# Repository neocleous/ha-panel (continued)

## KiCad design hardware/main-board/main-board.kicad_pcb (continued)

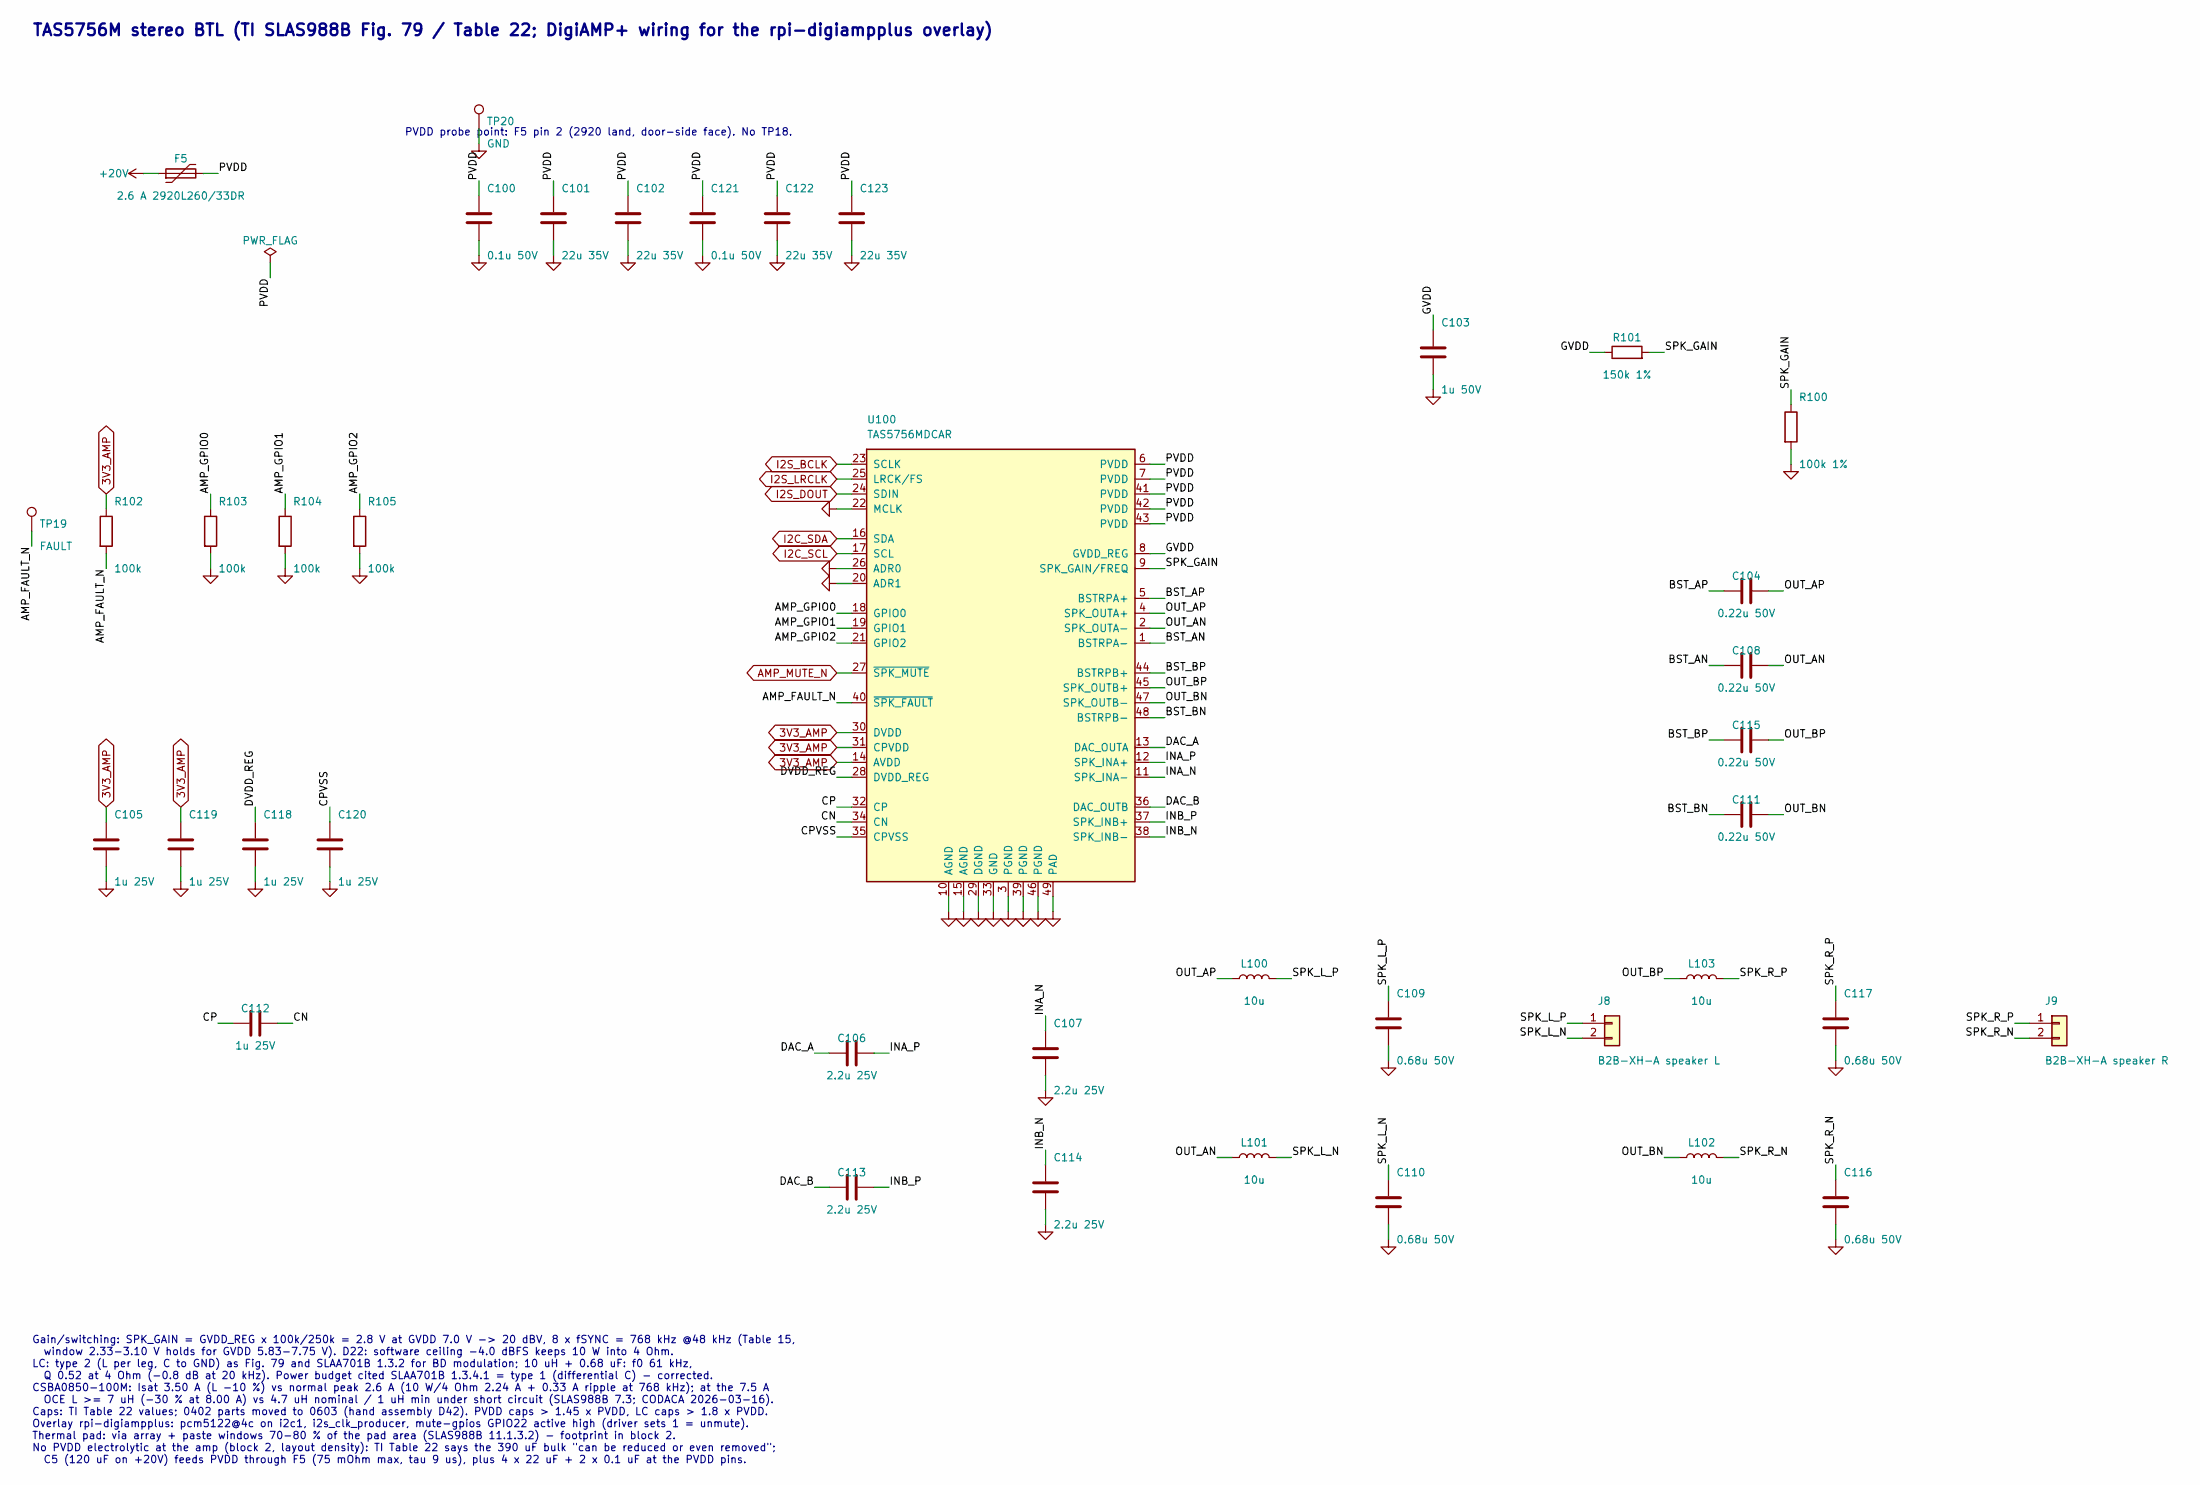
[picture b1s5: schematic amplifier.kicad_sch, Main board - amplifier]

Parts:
C100, C121: 0.1u 50V; C_0603_1608Metric; MPN CC0603KRX7R9BB104; DigiKey 311-1344-1-ND
C101, C102, C122, C123: 22u 35V; C_0805_2012Metric; MPN GMC21X5R226M35NT; DigiKey 4713-GMC21X5R226M35NTCT-ND
C103: 1u 50V; C_0603_1608Metric; MPN UMK107AB7105KA-T; DigiKey 587-3247-1-ND
C104, C108, C111, C115: 0.22u 50V; C_0603_1608Metric; MPN CL10B224KB8NNNC; DigiKey 1276-CL10B224KB8NNNCCT-ND
C105, C112, C118, C119, C120: 1u 25V; C_0603_1608Metric; MPN CC0603KRX7R8BB105; DigiKey 311-1802-1-ND
C106, C107, C113, C114: 2.2u 25V; C_0603_1608Metric; MPN CC0603KRX7R7BB225; DigiKey 311-3490-1-ND
C109, C110, C116, C117: 0.68u 50V; C_0805_2012Metric; MPN CL21B684KBFVPNE; DigiKey 1276-7009-1-ND
F5: 2.6 A 2920L260/33DR; Fuse_2920_7451Metric; MPN 2920L260/33DR; DigiKey 18-2920L260/33DRCT-ND
J8: B2B-XH-A speaker L; JST_XH_B2B-XH-A_1x02_P2.50mm_Vertical; MPN B2B-XH-A; DigiKey 455-B2B-XH-A-ND
J9: B2B-XH-A speaker R; JST_XH_B2B-XH-A_1x02_P2.50mm_Vertical; MPN B2B-XH-A; DigiKey 455-B2B-XH-A-ND
L100, L101, L102, L103: 10u; L_Codaca_CSBA0850; MPN CSBA0850-100M; DigiKey 4044-CSBA0850-100MCT-ND
R100: 100k 1%; R_0603_1608Metric; MPN RMCF0603FT100K; DigiKey RMCF0603FT100KCT-ND
R101: 150k 1%; R_0603_1608Metric; MPN RC0603FR-07150KL; DigiKey 311-150KHRCT-ND
R102, R103, R104, R105: 100k; R_0603_1608Metric; MPN RMCF0603FT100K; DigiKey RMCF0603FT100KCT-ND
TP19: FAULT; TestPoint_Pad_D1.5mm
TP20: GND; TestPoint_Pad_D1.5mm
U100: TAS5756MDCAR; TI_DCA0048A_HTSSOP-48-1EP; MPN TAS5756MDCAR; DigiKey 296-40565-1-ND

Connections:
3V3_AMP: C105.1, C119.1, R102.1, U100.14 (AVDD), U100.30 (DVDD), U100.31 (CPVDD); also elsewhere on the board
+20V: F5.1; also elsewhere on the board
/Amplifier/AMP_FAULT_N: R102.2, TP19.1, U100.40 (~SPK_FAULT)
/Amplifier/AMP_GPIO0: R103.1, U100.18 (GPIO0)
/Amplifier/AMP_GPIO1: R104.1, U100.19 (GPIO1)
/Amplifier/AMP_GPIO2: R105.1, U100.21 (GPIO2)
/Amplifier/BST_AN: C108.1, U100.1 (BSTRPA-)
/Amplifier/BST_AP: C104.1, U100.5 (BSTRPA+)
/Amplifier/BST_BN: C111.1, U100.48 (BSTRPB-)
/Amplifier/BST_BP: C115.1, U100.44 (BSTRPB+)
/Amplifier/CN: C112.2, U100.34 (CN)
/Amplifier/CP: C112.1, U100.32 (CP)
/Amplifier/CPVSS: C120.1, U100.35 (CPVSS)
/Amplifier/DAC_A: C106.1, U100.13 (DAC_OUTA)
/Amplifier/DAC_B: C113.1, U100.36 (DAC_OUTB)
/Amplifier/DVDD_REG: C118.1, U100.28 (DVDD_REG)
/Amplifier/GVDD: C103.1, R101.1, U100.8 (GVDD_REG)
/Amplifier/INA_N: C107.1, U100.11 (SPK_INA-)
/Amplifier/INA_P: C106.2, U100.12 (SPK_INA+)
/Amplifier/INB_N: C114.1, U100.38 (SPK_INB-)
/Amplifier/INB_P: C113.2, U100.37 (SPK_INB+)
/Amplifier/OUT_AN: C108.2, L101.1, U100.2 (SPK_OUTA-)
/Amplifier/OUT_AP: C104.2, L100.1, U100.4 (SPK_OUTA+)
/Amplifier/OUT_BN: C111.2, L102.1, U100.47 (SPK_OUTB-)
/Amplifier/OUT_BP: C115.2, L103.1, U100.45 (SPK_OUTB+)
/Amplifier/PVDD: C100.1, C101.1, C102.1, C121.1, C122.1, C123.1, F5.2, U100.6 (PVDD), U100.7 (PVDD), U100.41 (PVDD), U100.42 (PVDD), U100.43 (PVDD)
/Amplifier/SPK_GAIN: R100.1, R101.2, U100.9 (SPK_GAIN/FREQ)
/Amplifier/SPK_L_N: C110.1, J8.2, L101.2
/Amplifier/SPK_L_P: C109.1, J8.1, L100.2
/Amplifier/SPK_R_N: C116.1, J9.2, L102.2
/Amplifier/SPK_R_P: C117.1, J9.1, L103.2
AMP_MUTE_N: U100.27 (~SPK_MUTE); also elsewhere on the board
GND: C100.2, C101.2, C102.2, C103.2, C105.2, C107.2, C109.2, C110.2, C114.2, C116.2, C117.2, C118.2, C119.2, C120.2, C121.2, C122.2, C123.2, R100.2, R103.2, R104.2, R105.2, TP20.1, U100.3 (PGND), U100.10 (AGND), U100.15 (AGND), U100.20 (ADR1), U100.22 (MCLK), U100.26 (ADR0), U100.29 (DGND), U100.33 (GND), U100.39 (PGND), U100.46 (PGND), U100.49 (PAD); also elsewhere on the board
I2C_SCL: U100.17 (SCL); also elsewhere on the board
I2C_SDA: U100.16 (SDA); also elsewhere on the board
I2S_BCLK: U100.23 (SCLK); also elsewhere on the board
I2S_DOUT: U100.24 (SDIN); also elsewhere on the board
I2S_LRCLK: U100.25 (LRCK/FS); also elsewhere on the board

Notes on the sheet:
TAS5756M stereo BTL (TI SLAS988B Fig. 79 / Table 22; DigiAMP+ wiring for the rpi-digiampplus overlay)
PVDD probe point: F5 pin 2 (2920 land, door-side face). No TP18.
Gain/switching: SPK_GAIN = GVDD_REG x 100k/250k = 2.8 V at GVDD 7.0 V -> 20 dBV, 8 x fSYNC = 768 kHz @48 kHz (Table 15, window 2.33-3.10 V holds for GVDD 5.83-7.75 V). D22: software ceiling -4.0 dBFS keeps 10 W into 4 Ohm. LC: type 2 (L per leg, C to GND) as Fig. 79 and SLAA701B 1.3.2 for BD modula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

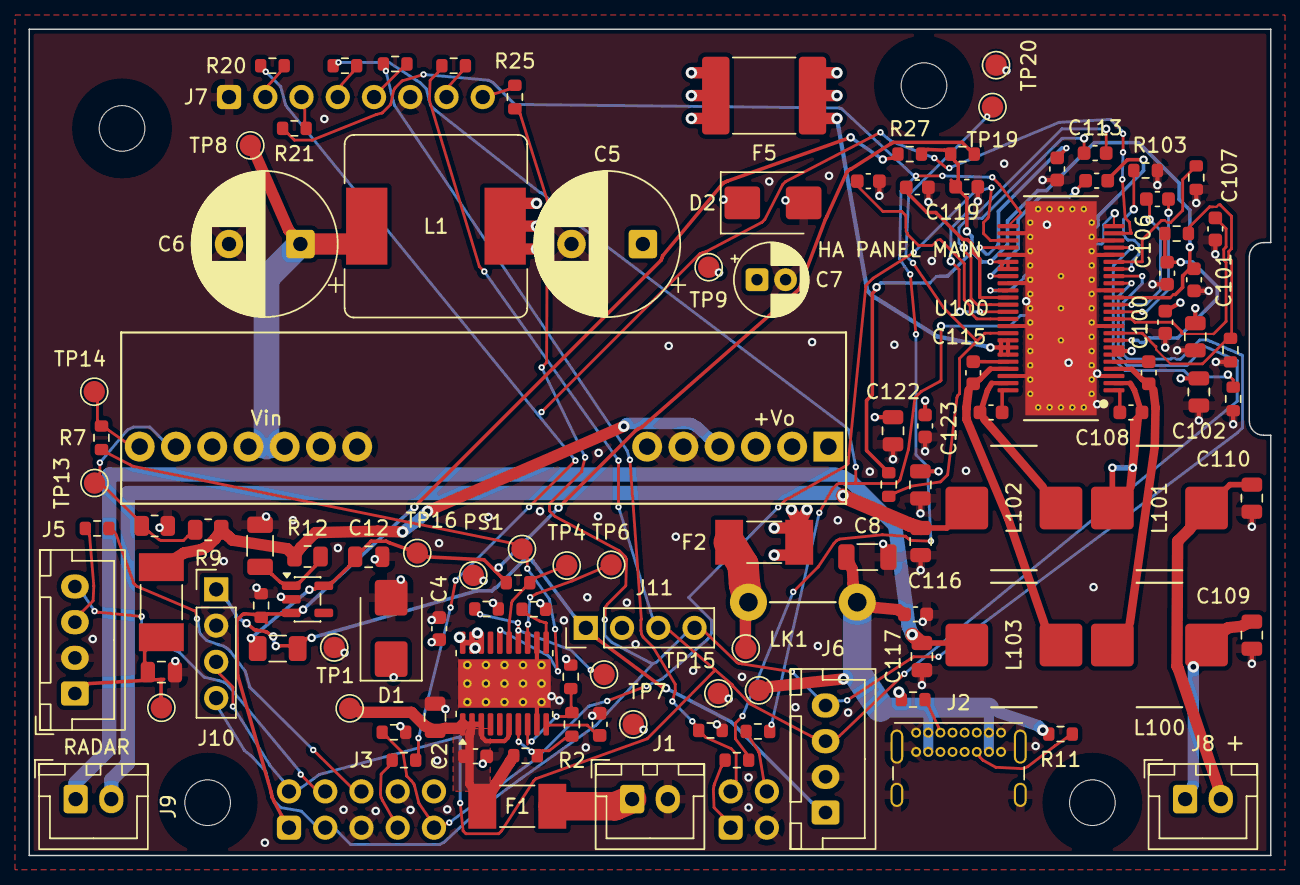
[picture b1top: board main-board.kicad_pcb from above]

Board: 4 copper layers, 87.0 x 57.9 mm, 120 parts (0 on the bottom side), 74 nets.

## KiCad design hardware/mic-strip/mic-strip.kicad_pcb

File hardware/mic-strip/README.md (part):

# HA panel — mic strip (two boards of one design)

Status: **block 3 done (2026-11-09) — fab files, assembly notes and drawing issued.** Decision 9 → **option 1** (Daniel, 2026-11-08): soldered wire pads instead of the JST connector. Decision 10 → **option 1** (Daniel, 2026-11-08): ESD321DYAR for D1–D3. JLC upload: **`fab/mic-strip-jlc-2026-11-09.zip`** (vias 0.5/0.3, D63 = b); order options in `../notes/jlc-fab.md` (0.8 mm, 2 layers, ENIG — Daniel, 2026-11-08). Assembly drawing: `mic-strip-assembly.pdf`; assembly and bring-up: below.

- **KiCad 9.0.9.** Open `mic-strip.kicad_pro`. Project libraries: `lib/ha_panel.kicad_sym` (IM69D120) and `lib/ha_panel.pretty` (IM69D120 land pattern, 5-pad wire column, heat-stake hole).
- **Schematic PDF:** `mic-strip-schematic.pdf`. **ERC:** 0 errors, 0 warnings (`erc-report.txt`).
- **DRC (2026-11-09, all severities):** 0 violations, 0 unconnected, 0 footprint errors, schematic parity clean (`drc-report.txt`). The check "footprint differs from library" is set to *ignore* in `mic-strip.kicad_pro`. U1's and MK1's silk marks at the board edge were removed on purpose, so both footprints differ from their library copies. These were the 2 warnings until 2026-11-08.
- **Renders:** `mic-strip-3d.png` (front = gasket side, back = parts) and `mic-strip-copper-F-B.png` (front copper, back copper mirrored). The copper picture shows the 2026-11-09 routing; the 3D render is from 2026-11-07, with the same parts and silk.
- **Generated by** `../main-board/gen/mic_strip.py` (schematic), `../main-board/gen/pcb_mic.py` (layout), `fix_esd321.py` (decision 10.1) and `reroute_strip_vias.py` (D63 = b). The KiCad files are the source of truth.

## Board (rev F K21 / "Top cap")
- **28 × 6 × 0.8 mm, 2 layers.** x = 0 at the outer (port) end. Every part sits on the **back** (inner side); the front faces the 1.0 mm gasket and carries only the GND pour and short crossings.
- **Port:** NPTH Ø0.8 at (2.0, 3.0), under MK1's sound port (rev F port at x_rel ±35.5, strip outer end ±37.5).
- **Heat-stake holes:** NPTH Ø2.0 at (7.5, 3.0) and (26.0, 3.0) for the Ø1.8 pins (x_rel ±30.0 / ±11.5); Ø3.6 back keep-outs (no copper, no parts) for the staked heads.
- One design for both sides: the left strip is the right one turned 180° in the cap plane (port end outward, gasket side up).
- **Rules:**
  - tracks 0.2 (0.25–0.3 for supply and ground), clearance 0.15, copper to edge 0.3;
  - **vias 0.5/0.3**, ring 0.10;
  - minimum via diameter 0.5 and minimum hole 0.3 (raised from 0.45 / 0.2 on 2026-11-09, so DRC flags any via outside JLC's free class);
  - hole clearance 0.25, hole to hole 0.25.
  - JLC capabilities checked 2026-11-07 and 2026-11-09 (`../notes/jlc-fab.md`).
- **Vias, D63 = (b) (Daniel, 2026-11-09):** **28 × 0.45/0.2 → 25 × 0.5/0.3.** JLC's order page states its 0.2 mm exemption only for multilayer boards; 0.3 mm holes are the free class.
  - Placement, parts, pads and silk are unchanged. Every track and via was re-routed by `reroute_strip_vias.py`, with the same connections and widths as `pcb_mic.py`.
  - Three fewer vias:
    - R2 (100 kΩ pull-down, no current) reaches GND through U1's ground on the back and has no via of its own. Its via was one of the two GND vias that a plain re-drill would have left 0.24 mm apart.
    - The back GND route from R2 to C1, which took two vias, is dropped. C1 has its own via and both pours carry ground.
  - One /MIC_LR vertex on the front was moved 0.05 mm inward to keep 0.3 from the edge.
  - **Achieved:**
    - ring 0.10;
    - via hole to hole ≥ 0.45 (different nets; JLC 0.2);
    - via hole to NPTH ≥ 0.56;
    - via hole to other-net track ≥ 0.29 and to other-net pad ≥ 0.33 (board 0.25; JLC 0.2).

## Circuit (E0-D6, decisions 8.1 and 9.1)
| Ref | Part | Default | Why / source |
|---|---|---|---|
| J1 | 5 SMD wire pads 2.0 × 0.7, 1.1 mm pitch, one column across the strip | — | Decision 9.1: the BM05B-SRSS-TB (8.89 mm courtyard) does not fit beside the parts. Cable JST A05SR05SR30K305B with both housings cut off, conductors soldered in cable order **1 VDD, 2 GND, 3 CLK, 4 SEL, 5 DATA**; hot-melt strain relief over the pads. The pads are also the test points. |
| D1–D3 | TI ESD321DYAR, SOD-523 | fitted | ESD on VDD, CLK, DATA next to the cable pads. Decision 10.1: replaces TPD1E05U06DYAR (DigiKey 0 stock, 26 weeks, 2026-11-08). 0.9 pF typ / 1.1 pF max, VRWM 3.6 V above the 3.3 V lines. **DYA pinout: pin 1 = GND, pin 2 = IO** — the reverse of the TPD1E05U06, so the footprints are turned 180° (copper unchanged). Pin 1 is the end marked by the dot on the body (TI marks the DYA pin 1 with a circular notch, not a line); it goes to the closed end of the silk bracket, the GND pad at x 19.8. Check after soldering, meter in diode mode: red on the GND pad, black on the signal pad → conducts; reversed → open. Generated by `../main-board/gen/fix_esd321.py`. |
| R1 | 100 Ω 0603 | fitted | VDD RC filter with C1: f_c = 159 Hz; drop ≈ 0.1 V at the mic's 980 µA. |
| C1, C2 | 10 µF 10 V X5R 0603, 100 nF 50 V X7R 0603 | fitted | Mic decoupling (E0-D6); C2 next to MK1's VDD pin. |
| U1 | TI SN74LVC1G17DCKR, SC-70-5 | fitted | Schmitt buffer re-drives CLK next to the mic (E0-D6). C3 100 nF at VCC. Bypass lever (bench 2.5): remove U1 and bridge its pads 2–4 with wire — R3 (the 0 Ω bypass position) was dropped for space. |
| R2 | 100 kΩ 0603 | fitted | Weak pull-down on the buffer input (CLK may be tri-stated when muted — inference). |
| MK1 | Infineon IM69D120V01XTSA1 | fitted | Decision 8.1. Bottom port, −26 dBFS ±1, SNR 69 dB(A), 3.072 MHz inside its 2.9–3.3 MHz range, clock duty 48–52 %, 980 µA typ, VDD 1.62–3.6 V (datasheet rev 1.0, 2017-12-20). DigiKey IM69D120V01XTSA1CT-ND. |
| R4 | 33 Ω 0603 | fitted | DATA source termination (100 Ω alternative, bench 2.5 lever). |
| R5 | 0 Ω 0603 | fitted | **L/R from the cable SEL wire**, strapped at the ReSpeaker end (vacated mic pad 5): GND = left, VDD = right. Must be fitted on both strips — there is no on-board strap any more (JP1 dropped, decision 9.1). |

Removed against checkpoint 1: J1 connector, JP1, TP1–TP4 (decision 9.1), R3 (space); MSM261DHP006 replaced by the IM69D120 (decision 8.1); TPD1E05U06DYAR replaced by the ESD321DYAR (decision 10.1).

Cable termination at the ReSpeaker (bench plan "connect by function"): VDD → pad 1, CLK → pad 2, DATA → pad 3, GND → pad 4 (and 6), **SEL → pad 5**. SEL is static and sits between CLK and DATA in the cable.

Sources (read 2026-11-07, assembly notes 2026-11-09): Infineon IM69D120 datasheet rev 1.0 (2017-12-20); TI SN74LVC1G17 SCES351Y (https://www.ti.com/lit/ds/symlink/sn74lvc1g17.pdf); TI TPD1E05U06 SLVSBO7O (https://www.ti.com/lit/ds/symlink/tpd1e05u06.pdf); read 2026-11-08: TI ESD321 datasheet rev C, 2025-06-04 (https://www.ti.com/lit/ds/symlink/esd321.pdf, table 4-2) and TI E2E on the DYA pin-1 mark (https://e2e.ti.com/support/interface-group/interface/f/interface-forum/1410599/esd321-pin1-position, https://e2e.ti.com/support/interface-group/interface/f/interface-forum/1449663/esd321-pin-1-clarify); rev F geometry from `claude/enclosure-v5-revF-2026-11-03.md` (Top: mic strips) and `claude/enclosure-v5-revF-audit-response-2026-11-06.md` (finding 38); cable from `claude/E0-order-list-2026-11-01.md` rev 4; JLC capabilities https://jlcpcb.com/capabilities.

## Assembly (block 3, 2026-11-09) — build two identical strips
Drawing: `mic-strip-assembly.pdf` (back, as seen from the back). One hotplate pass, parts side up.

**Before you start**
- Paste: the same Sn63/Pb37 no-clean as the main board, dispensed by syringe. The combined stencil has no strip area (`../notes/jlc-fab.md`).
- Bare strip:
  - hold it against the light: the Ø0.8 port hole must be open;
  - meter: VDD–GND (J1 pads 1–2) open.
- **What the makers say about the port:**
  - Infineon's IM69D120 datasheet (rev 1.0) gives only the reflow qualification: 3 reflows, peak 260 °C, IPC/JEDEC J-STD-020D-01. It has no handling, flux or washing rules.
  - Other makers' bottom-port MEMS guides agree:
    - TDK/InvenSense: water must not reach the port when washing; no blow-off, no ultrasonic cleaning.
    - InvenSense AN-100: the port is sensitive to solder flux.
    - ST: seal the port with tape during soldering.
  - So: no-clean paste, **no washing, no IPA or air near the port**, and Kapton tape over the hole on the front while soldering.

**Build order**
1. Kapton over the port hole on the front (gasket side).
2. Small paste dots on the back pads. Nothing in or next to the port hole.
3. Place:
   - D1–D3 ESD321: pin 1 = GND (dot or notch on the body), at the closed end of the silk bracket;
   - C1 10 µF, C2 100 nF, C3 100 nF;
   - R1 100 Ω, R2 100 kΩ, R4 33 Ω, R5 0 Ω (**required**);
   - U1 SN74LVC1G17 (pin 1 at the chamfer);
   - MK1 last, lid up, port over the hole. Handle it by the lid only.
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
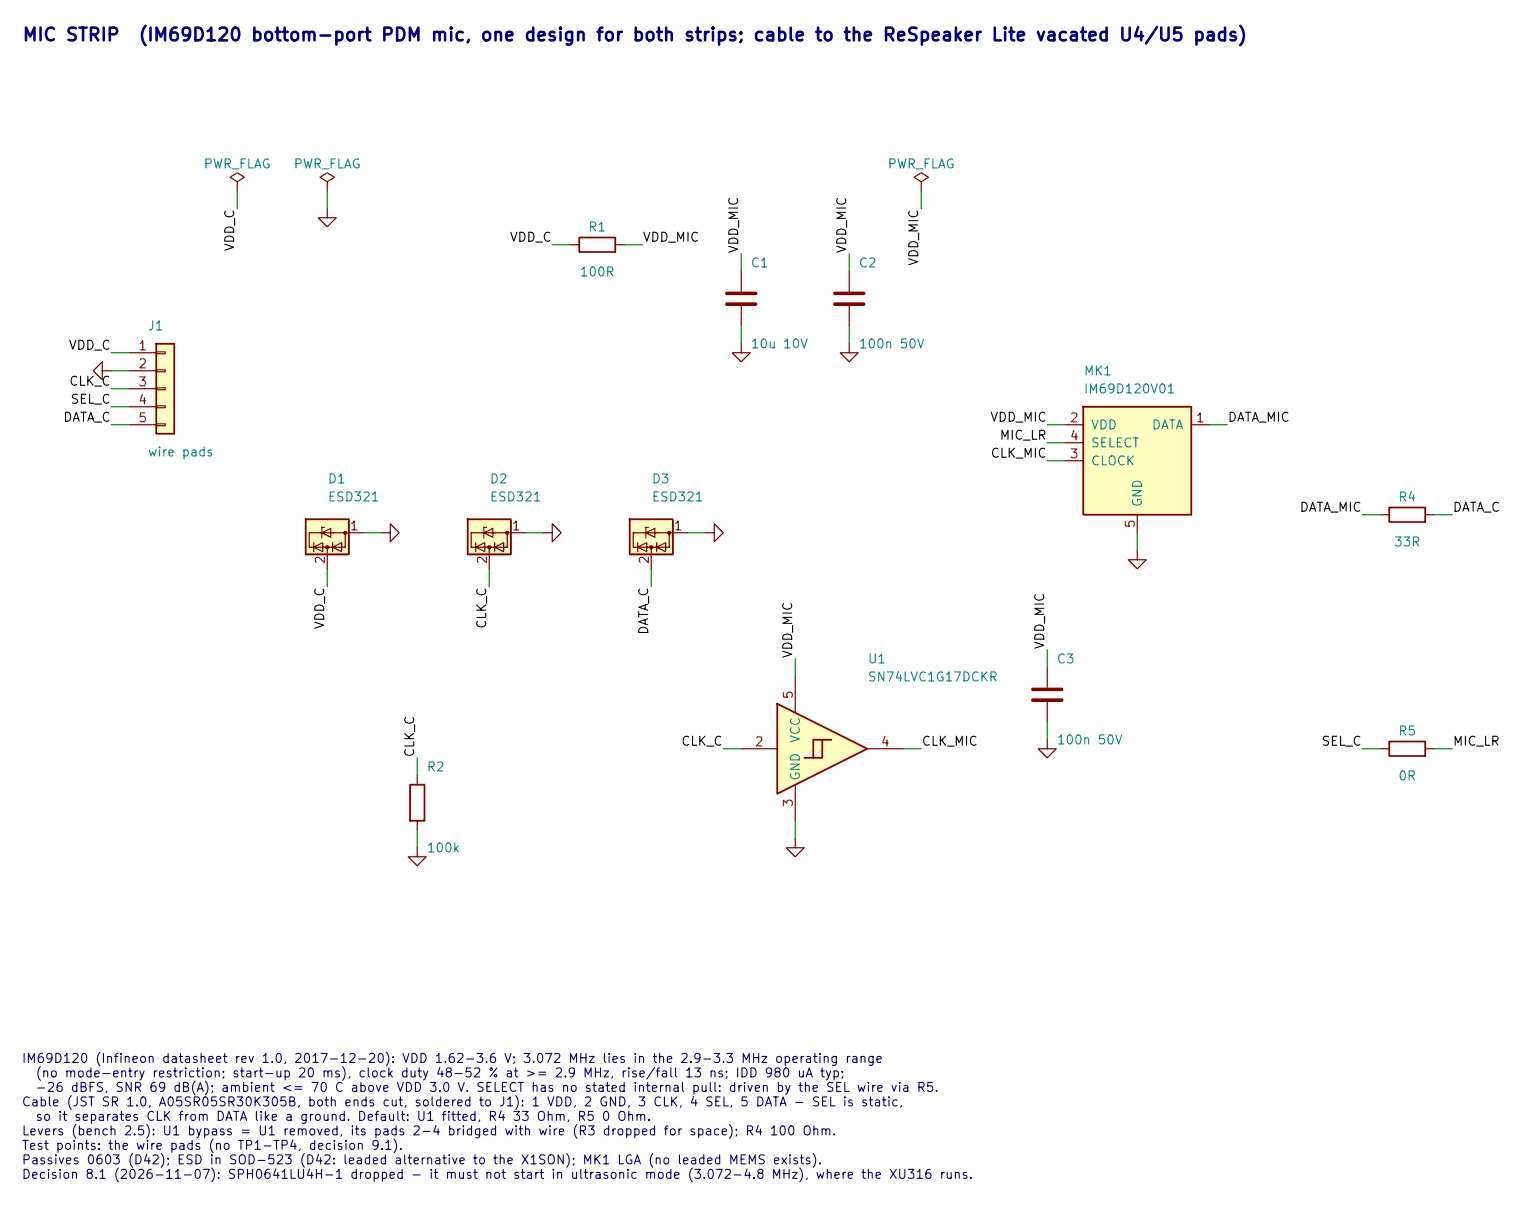
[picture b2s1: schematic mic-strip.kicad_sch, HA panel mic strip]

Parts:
C1: 10u 10V; C_0603_1608Metric; MPN EMK107BBJ106MA-T; DigiKey 587-3238-1-ND
C2, C3: 100n 50V; C_0603_1608Metric; MPN CC0603KRX7R9BB104; DigiKey 311-1344-1-ND
D1, D2, D3: ESD321; D_SOD-523; MPN ESD321DYAR; DigiKey 296-ESD321DYARCT-ND
J1: wire pads; WirePads_1x05_P1.10mm_2.0x0.7mm
MK1: IM69D120V01; Infineon_IM69D120_PG-LLGA-5-1; MPN IM69D120V01XTSA1; DigiKey IM69D120V01XTSA1CT-ND
R1: 100R; R_0603_1608Metric; MPN RMCF0603FT100R; DigiKey RMCF0603FT100RCT-ND
R2: 100k; R_0603_1608Metric; MPN RMCF0603FT100K; DigiKey RMCF0603FT100KCT-ND
R4: 33R; R_0603_1608Metric; MPN RMCF0603FT33R0; DigiKey RMCF0603FT33R0CT-ND
R5: 0R; R_0603_1608Metric; MPN RC0603JR-070RL; DigiKey 311-0.0GRCT-ND
U1: SN74LVC1G17DCKR; SOT-353_SC-70-5; MPN SN74LVC1G17DCKR; DigiKey 296-11934-1-ND

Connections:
/CLK_C: D2.2 (I/O), J1.3, R2.1, U1.2
/CLK_MIC: MK1.3 (CLOCK), U1.4
/DATA_C: D3.2 (I/O), J1.5, R4.2
/DATA_MIC: MK1.1 (DATA), R4.1
/MIC_LR: MK1.4 (SELECT), R5.2
/SEL_C: J1.4, R5.1
/VDD_C: D1.2 (I/O), J1.1, R1.1
/VDD_MIC: C1.1, C2.1, C3.1, MK1.2 (VDD), R1.2, U1.5 (VCC)
GND: C1.2, C2.2, C3.2, D1.1 (GND), D2.1 (GND), D3.1 (GND), J1.2, MK1.5 (GND), R2.2, U1.3 (GND)

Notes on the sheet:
MIC STRIP (IM69D120 bottom-port PDM mic, one design for both strips; cable to the ReSpeaker Lite vacated U4/U5 pads)
IM69D120 (Infineon datasheet rev 1.0, 2017-12-20): VDD 1.62-3.6 V; 3.072 MHz lies in the 2.9-3.3 MHz operating range (no mode-entry restriction; start-up 20 ms), clock duty 48-52 % at >= 2.9 MHz, rise/fall 13 ns; IDD 980 uA typ; -26 dBFS, SNR 69 dB(A); ambient <= 70 C above VDD 3.0 V. SELECT has no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

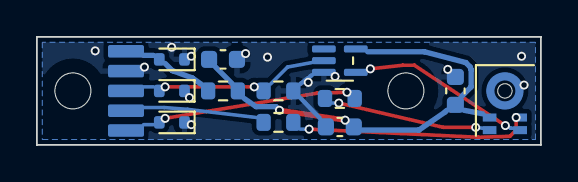
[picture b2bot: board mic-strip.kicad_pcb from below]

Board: 2 copper layers, 28.0 x 6.0 mm, 15 parts (13 on the bottom side), 9 nets.

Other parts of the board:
HS1, HS2: heat stake; HeatStake_D2.0mm_Head3.6mm

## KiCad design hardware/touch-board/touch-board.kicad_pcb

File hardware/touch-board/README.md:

# HA panel — touch board rev D (decision 5A, 2026-11-07)

Replaces rev C (`hardware/rev-c`, unchanged) in the rev F chin seat: same 90 × 44 × 1.6 outline, R2 corners, no holes
except tented vias, flat front. Generated by `hardware/main-board/gen/touch_board.py` (schematic) and `pcb_touch.py`
(layout). KiCad 9.0.9. ERC 0 errors / 0 warnings; DRC (all severities, with schematic parity) 0 violations, 0 unconnected,
0 footprint errors (2026-11-09; `fix_touch_fpid.py` gave every footprint its library nickname, which cleared 12 parity
warnings the error-only DRC had not shown).

| Item | Value | Source |
|---|---|---|
| Controller | AT42QT1070 SOIC-14, comms (I²C) mode, address 0x1B; MODE (pin 2) to GND; RESET, CHANGE, KEY4–6 open | Atmel 9596C–AT42–05/2013 table 1-1 |
| Electrodes | 4 × 16 × 16 mm, r 2, front copper under the mask; centres front-view X 9/33/57/81, Y 13 (rev F) | QTAN0062 §2.3: electrode ≥ 4 × panel thickness; panel ≈ 2.5 wall + 0.7 cloth = 3.2 mm (rev F model, not measured) → ≥ 12.8 mm. Rev C: Ø12 |
| Key order | seen from the front, left to right **KEY0, KEY1, KEY2, KEY3** — the same order as rev C rotated into rev F, so the rev F mapping in `at42qt1070.py` applies unchanged | |
| Series R | R1–R4 4.7 kΩ 0603, next to U1 | datasheet §3.1 |
| Decoupling | C1 100 nF + C2 10 µF 0603 | |
| HOST pads | J1, SMD wire pads 2 × 3 mm at 3.5 pitch on the back, front-view (33, 39.8) as rev F: VCC, GND, SDA, SCL (labelled); lead from main board J6 | rev F lead TOUCH unchanged |
| Sensors | none — the BME680 and VEML6030 leads land on main-board J10 (decision 5A); VL53L0X cluster dropped | |
| Pull-ups | none on this board (Pi 1.8 kΩ) | |
| Cx | AT42QT1070 accepts 1–30 pF per key | datasheet 6.2 |

Layout: front copper = electrodes only. Back: U1, R1–R4, C1, C2, J1 pads, all traces (0.25 mm signal, 0.4 mm supply),
B.Cu track keep-outs behind the electrodes, electrode vias at each electrode's top edge (tented).

**Assembly (2026-11-09).** One SMD side, the back. Drawing: `touch-board-assembly.pdf` (back, as seen from the back).
1. Bare board: VCC–GND on the HOST pads must read open.
2. Paste the back through the touch area of the combined stencil (`../stencil/`).
   - Use the stencil the same way up as for the main board: the touch pattern is already mirrored to match the back seen from above.
   - The HOST pads get no paste.
3. Place U1 (pin 1 at the chamfered corner), C1 100 nF, C2 10 µF, R1–R4 4.7 kΩ.
4. Hotplate with the front face down on a clean sheet (the front has no parts). Same paste and profile as the main board (`../main-board/README.md`).
5. Solder the touch lead to the HOST pads with the iron: VCC, GND, SDA, SCL as labelled. Lead: XH 4P from main-board J6, cut ≈ 105 (`../notes/harness.md`).
6. Bring-up: VCC–GND not shorted; then, on the Pi, `sudo i2cdetect -y 1` shows **1b**.

Files: `touch-board.kicad_sch/.kicad_pcb/.kicad_pro`, `lib/` (ha_panel symbol + footprints), `touch-board-schematic.pdf`,
`erc-report.txt`, `drc-report.txt`, `touch-board-front.png`, `touch-board-back.png`.

**Fab (JLC, bare board; D57):** `fab/touch-board-jlc-2026-11-09.zip` (gerbers and drill, unzipped in `fab/gerbers/`;
`fab/drill-report.txt`: 4 plated holes Ø0.30, the tented electrode vias; no NPTH). 2 layers, 1.6 mm, ENIG, 90 × 44.
Order options and limits: `../notes/jlc-fab.md`. **Paste:** the touch board's back pattern is on the combined stencil
with the main board's front (`../stencil/`); don't tick the stencil box on the touch-board line.

**Purchase fields** (in the schematic; `gen/bom_fields_touch.json`):

| Ref | Part | Source |
|---|---|---|
| U1 | Microchip AT42QT1070-SSUR | Daniel's own stock (D56): none in the DigiKey basket |
| C1 | Yageo CC0603KRX7R9BB104, 100 nF 50 V X7R | DigiKey 311-1344-1-ND, basket line shared with the main board and the strip |
| C2 | Taiyo Yuden EMK107BBJ106MA-T, 10 µF 16 V X5R | DigiKey 587-3238-1-ND, basket line shared with the strip |
| R1–R4 | Yageo RC0603FR-074K7L, 4.7 kΩ 1 % | DigiKey 311-4.70KHRCT-ND, basket line shared with the main board |
| J1 | bare wire pads | — |
| E0–E3 | copper electrodes | — |

The basket lines' quantities already cover these parts within the spares rule (`../notes/digikey-bom.md`).

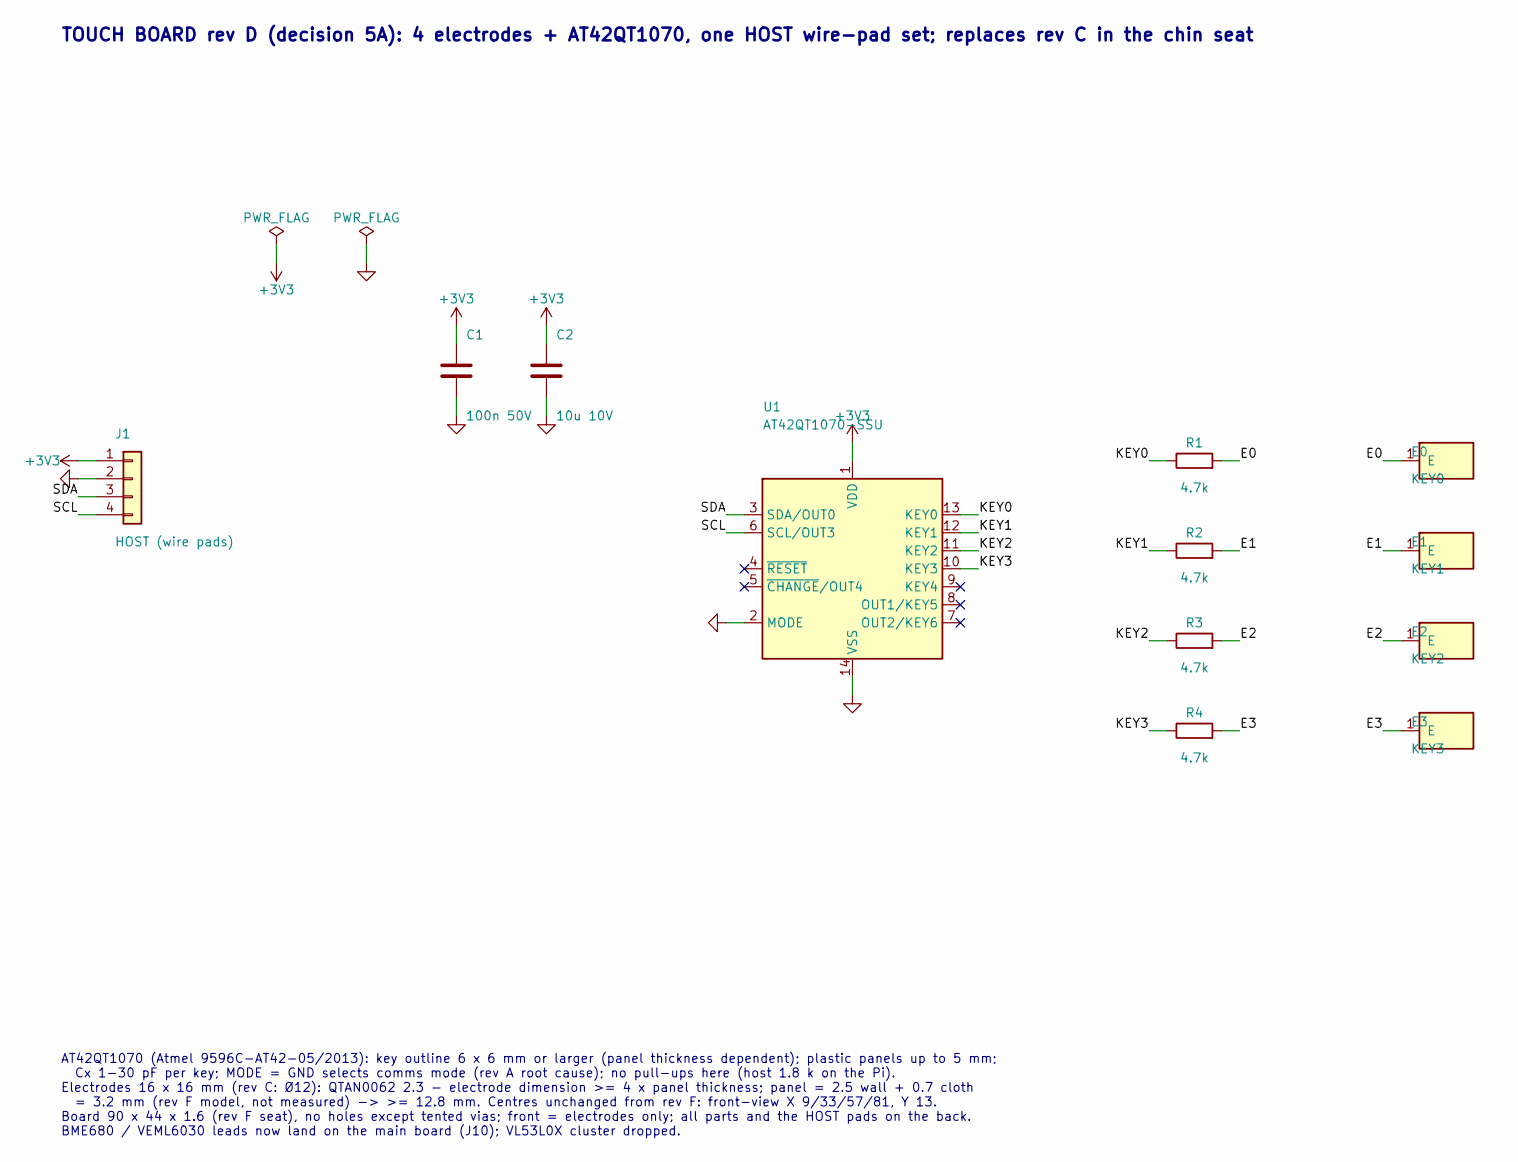
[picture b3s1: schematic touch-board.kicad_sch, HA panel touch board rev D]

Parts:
C1: 100n 50V; C_0603_1608Metric; MPN CC0603KRX7R9BB104; DigiKey 311-1344-1-ND
C2: 10u 10V; C_0603_1608Metric; MPN EMK107BBJ106MA-T; DigiKey 587-3238-1-ND
E0: KEY0; TouchElectrode_16x16mm_R2
E1: KEY1; TouchElectrode_16x16mm_R2
E2: KEY2; TouchElectrode_16x16mm_R2
E3: KEY3; TouchElectrode_16x16mm_R2
J1: HOST (wire pads); WirePads_1x04_P3.50mm_2.0x3.0mm
R1, R2, R3, R4: 4.7k; R_0603_1608Metric; MPN RC0603FR-074K7L; DigiKey 311-4.70KHRCT-ND
U1: AT42QT1070-SSU; SOIC-14_3.9x8.7mm_P1.27mm; MPN AT42QT1070-SSUR; DigiKey none - from Daniel's stock (D56)

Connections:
+3V3: C1.1, C2.1, J1.1, U1.1 (VDD)
/E0: E0.1, R1.2
/E1: E1.1, R2.2
/E2: E2.1, R3.2
/E3: E3.1, R4.2
/KEY0: R1.1, U1.13 (KEY0)
/KEY1: R2.1, U1.12 (KEY1)
/KEY2: R3.1, U1.11 (KEY2)
/KEY3: R4.1, U1.10 (KEY3)
/SCL: J1.4, U1.6 (SCL/OUT3)
/SDA: J1.3, U1.3 (SDA/OUT0)
GND: C1.2, C2.2, J1.2, U1.2 (MODE), U1.14 (VSS)

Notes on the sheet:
TOUCH BOARD rev D (decision 5A): 4 electrodes + AT42QT1070, one HOST wire-pad set; replaces rev C in the chin seat
AT42QT1070 (Atmel 9596C-AT42-05/2013): key outline 6 x 6 mm or larger (panel thickness dependent); plastic panels up to 5 mm; Cx 1-30 pF per key; MODE = GND selects comms mode (rev A root cause); no pull-ups here (host 1.8 k on the Pi). Electrodes 16 x 16 mm (rev C: Ø12): QTAN0062 2.3 - electrode d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

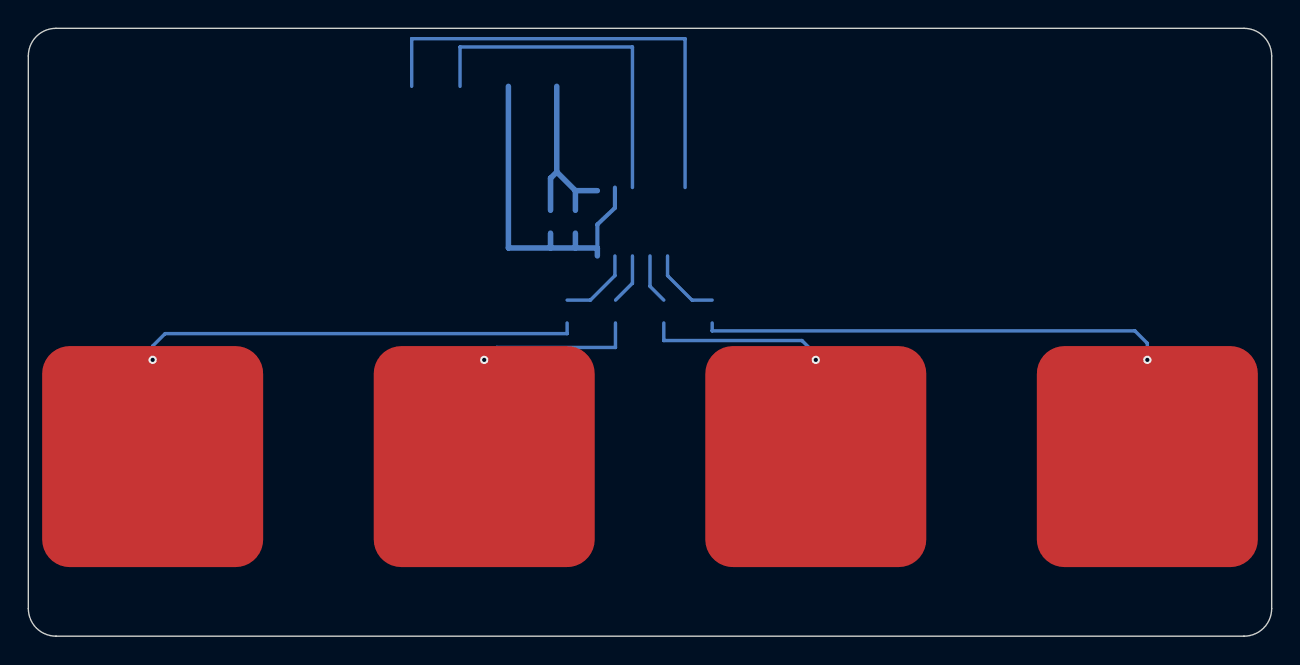
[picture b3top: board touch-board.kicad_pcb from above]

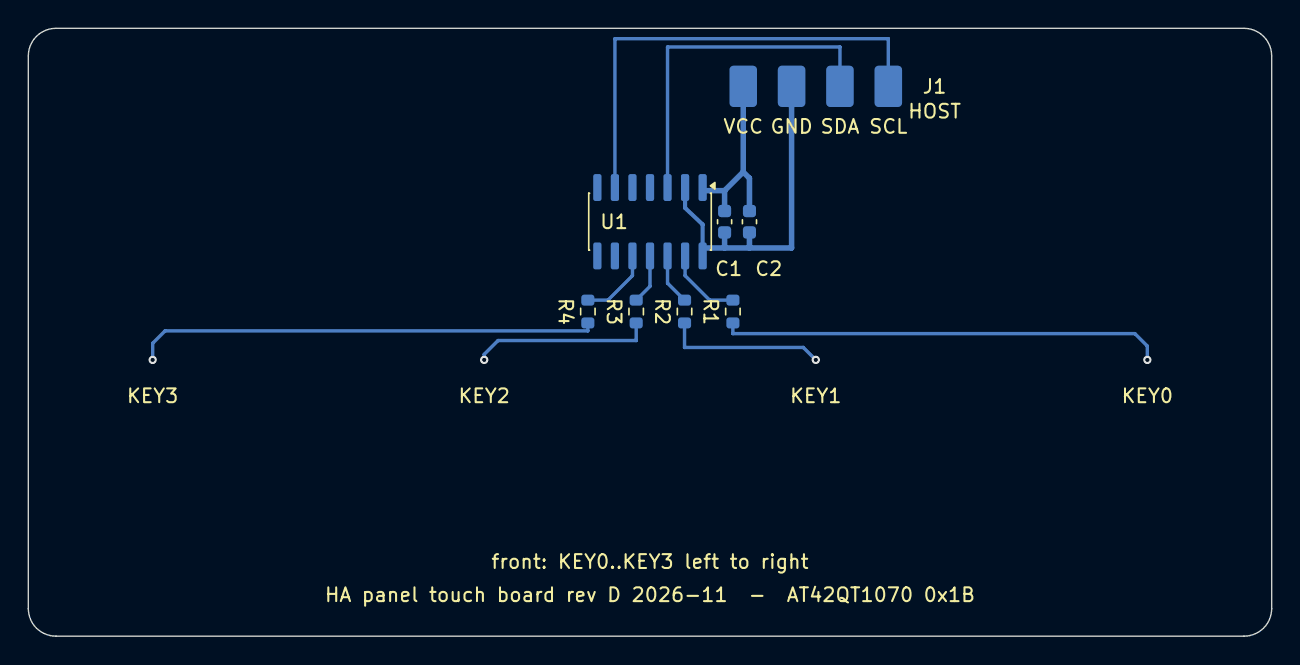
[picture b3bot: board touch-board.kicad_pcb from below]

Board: 2 copper layers, 90.0 x 44.0 mm, 12 parts (8 on the bottom side), 12 nets.

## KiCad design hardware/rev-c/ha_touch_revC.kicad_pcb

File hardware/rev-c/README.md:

# HA Panel — Touch Board rev C

Capacitive 4-button touch board for the wall-mounted Home Assistant panel.
Carries the touch controller and acts as the wiring hub for the panel's I2C
sensor breakouts. Designed 2026-07; fabricated at JLCPCB.

Rev C is a ground-up redesign (KiCad 7, programmatically generated) replacing
the rev-A/rev-B EasyEDA design.

## Specifications

| Parameter | Value |
|---|---|
| Dimensions | 100 x 44 mm, rounded corners r2, 1.6 mm FR-4 |
| Layers | 2 (front: electrodes + bus, back: all components) |
| Finish | ENIG, green mask, white silk |
| Holes | None (tented vias only) — front face is completely flat |
| Touch controller | AT42QT1070-SSUR (SOIC-14), I2C addr 0x1B |
| Electrodes | 4x Ø12 mm top copper, mask-covered (intentional — no exposed metal), 24 mm pitch |
| I2C | No on-board pull-ups; bus relies on host (Pi 1.8k) + breakout pull-ups |

## Design notes / changes vs rev A

- **MODE (pin 2) tied to GND** — hard requirement for I2C mode. Floating MODE
  was the probable root cause of rev A never appearing at 0x1B.
- **4.7k series resistors (R1–R4) added in each KEY sense line** per
  AT42QT1070 datasheet §3.1 (ESD/RFI). Rev A had none.
- **4.7k series resistors in SDA/SCL removed** — with the Pi's 1.8k hardware
  pull-ups they broke logic levels (V_OL ≈ 2.4 V at the host).
- Unused pins (KEY4–6, RESET#, CHANGE#) left unconnected per datasheet;
  disable keys 4–6 in software (AVE/AKS = 0).
- All silkscreen is human-readable: every part carries designator + value,
  every wire pad is net-labelled, U1 has a pin-1 dot.

## Wire pad clusters (bottom edge, viewed from the back)

Left to right: **HOST (PI)** · **BME680** · **VL53L0X** · **VEML6030**
Each cluster: `VCC  GND  SDA  SCL` (labelled). Pads 2x3 mm, 3.5 mm pitch,
sized for 24 AWG (power) / 28 AWG (signal) silicone stranded wire.

All three sensor clusters are parallel drops on the same I2C bus
(0x77 / 0x29 / 0x48; controller at 0x1B — no conflicts).

## Electrode / key mapping

Viewed from the FRONT of the panel, left to right the electrodes are
**KEY3, KEY2, KEY1, KEY0** (routing-optimised order). Map keys to actions
in `sensor-daemon` accordingly.

## Assembly

1. Stencil (bottom side, 0.12 mm) + Sn63/Pb37 no-clean paste (SMD291AXT4).
   Paste apertures exist only for U1, R1–R4, C1, C2 — wire pads are
   intentionally paste-free.
2. Place: U1 (mind the pin-1 dot), 4x 4k7 0402, C1 100n 0402, C2 10u 0603.
3. Hot air ~320 °C, low-mid airflow, until reflow + a few seconds.
4. Solder harness wires to the clusters with an iron (pre-tin wire + pad).
5. Bring-up: power via HOST cluster, then `sudo i2cdetect -y 1` on the Pi —
   0x1B present validates MODE strap, solder and bus in one shot.

## Files

- `ha_touch_revC.kicad_pcb` — board source (KiCad 7). DRC-clean. This is
  the canonical file; the fabrication set regenerates from it exactly:
  `kicad-cli pcb export gerbers ha_touch_revC.kicad_pcb -o gerbers/ \
   --layers "F.Cu,B.Cu,F.Mask,B.Mask,F.SilkS,B.SilkS,B.Paste,Edge.Cuts" \
   --subtract-soldermask` plus
  `kicad-cli pcb export drill --format excellon --excellon-separate-th`.
  The zip as actually ordered (2026-07-26) is archived offline.
- `BOM.csv` — bill of materials with DigiKey part numbers.

JLCPCB order settings: 2 layer, 1.6 mm, ENIG, tented vias, remove mark,
flying-probe test; stencil bottom-only, custom 190x190 mm.

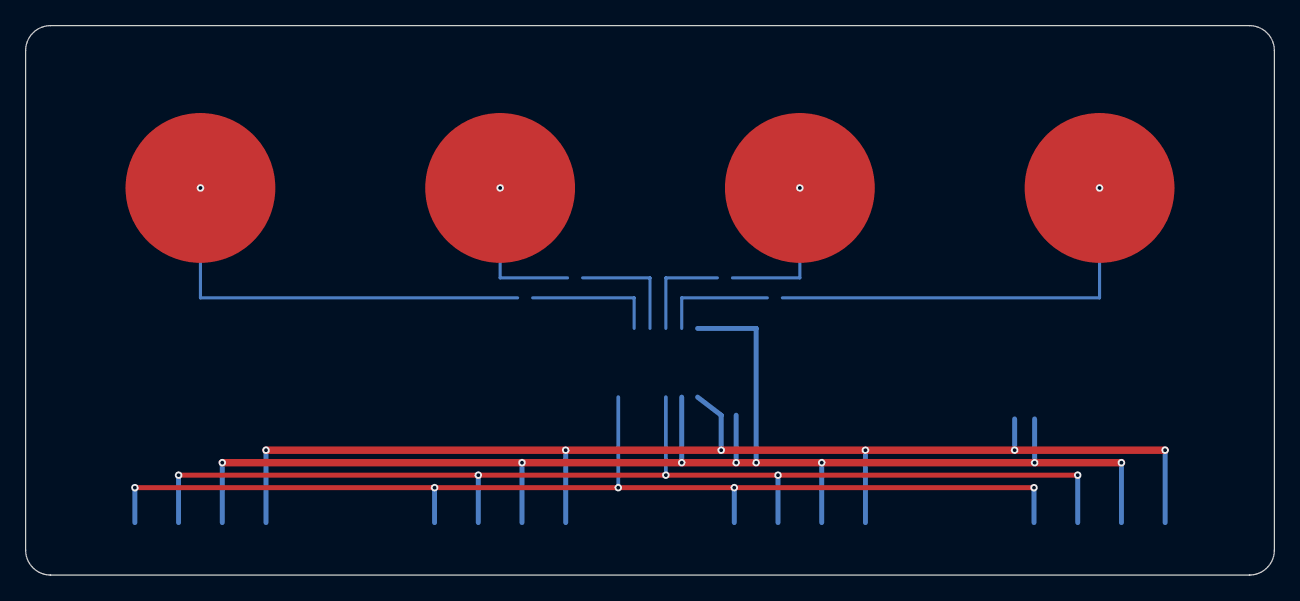
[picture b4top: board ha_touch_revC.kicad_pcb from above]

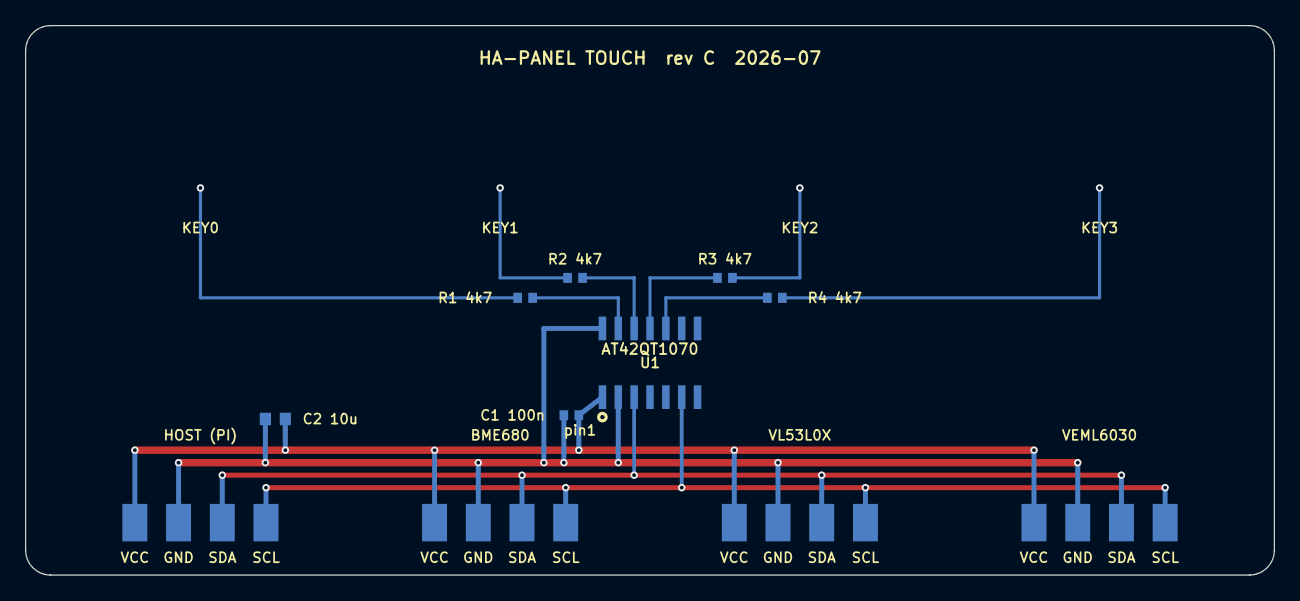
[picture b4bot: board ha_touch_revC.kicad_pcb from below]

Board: 2 copper layers, 100.0 x 44.0 mm, 15 parts (11 on the bottom side), 12 nets.

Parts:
C1: C1
C2: C2
E0: E0
E1: E1
E2: E2
E3: E3
J1: J1
J2: J2
J3: J3
J4: J4
R1: R1
R2: R2
R3: R3
R4: R4
U1: U1

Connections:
GND: C1.2, C2.2, J1.2, J2.2, J3.2, J4.2, U1.2, U1.14
KEY0: R1.1, U1.13
KEY1: R2.1, U1.12
KEY2: R3.2, U1.11
KEY3: R4.2, U1.10
SCL: J1.4, J2.4, J3.4, J4.4, U1.6
SDA: J1.3, J2.3, J3.3, J4.3, U1.3
SENSE0: E0.1, R1.2
SENSE1: E1.1, R2.2
SENSE2: E2.1, R3.1
SENSE3: E3.1, R4.1
VCC: C1.1, C2.1, J1.1, J2.1, J3.1, J4.1, U1.1

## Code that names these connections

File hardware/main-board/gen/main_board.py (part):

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        '  STANDBY (Pi 3V3 off, 5 V on, HAT+ spec 2.2): LDO off -> no back-feed through I2C; amp muted by R17.',
        'R26/R27: amp logic rail 3V3_AMP from the LDO (default, R26) or from the Pi 3V3 (R27): TAS5756M VIH = 0.9 x DVDD',
        '  (SLAS988B 7.3) and TI advises driving its inputs from the DVDD supply; LDO +-1 % (SBVS186H) vs Pi 3V3 (not published).',
        'Pi pins: 3/5 SDA/SCL (GPIO2/3, 1.8 k pull-ups on the Pi); 8/10 TXD/RXD (GPIO14/15, uart0);',
        '  12/35/38/40 = GPIO18/19/20/21 I2S BCLK/LRCLK/DIN/DOUT; 15 = GPIO22 amp mute (rpi-digiampplus).',
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        'Sensor branch 3V3_SENS (F4 0.2 A PTC): J6 touch board, J10 BME680, J11 VEML6030 (one 1 x 4 header each, rev 3).',
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           footprint='Fuse:Fuse_2920_7451Metric',
           fields=F('2920L260/33DR', 'Littelfuse', '18-2920L260/33DRCT-ND', 'PTC 2.6 A hold (1.81 A at 60 C), 33 V, R1max 75 mOhm'))
    s.pwr_flag('PVDD', (66.04, 60.96))
    s.text('PVDD probe point: F5 pin 2 (2920 land, door-side face). No TP18.',
           88.9, 38.1, size=1.27)
    # PVDD decoupling (left side pins 6/7 and right side 41-43)
    for i, (ref, val, fp, spec) in enumerate([('C100', '0.1u 50V', C0603, '0.1 uF 50 V X7R 0603'),
                                              ('C101', '22u 35V', C0805, '22 uF 35 V X5R 0805'),
                                              ('C102', '22u 35V', C0805, '22 uF 35 V X5R 0805'),
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                                              ('C123', '22u 35V', C0805, '22 uF 35 V X5R 0805')]):
        mpn = ('GMC21X5R226M35NT', 'Cal-Chip', '4713-GMC21X5R226M35NTCT-ND') if val.startswith('22u') else ('', '', '')
        s.comp(ref, 'Device:C', val, (101.6 + i * 12.7, 53.34), nets={'1': 'PVDD', '2': 'GND'}, footprint=fp,
               fields=F(mpn[0], mpn[1], mpn[2], spec, 'PVDD pins 6/7 (C100-C102) and 41-43 (C121-C123): place at the pins'))
    s.comp('U100', 'ha_panel:TAS5756M', 'TAS5756MDCAR', (190.5, 129.54),
           nets={'23': 'I2S_BCLK', '25': 'I2S_LRCLK', '24': 'I2S_DOUT', '22': 'GND',
                 '16': 'I2C_SDA', '17': 'I2C_SCL', '26': 'GND', '20': 'GND',
                 '18': 'AMP_GPIO0', '19': 'AMP_GPIO1', '21': 'AMP_GPIO2',
                 '27': 'AMP_MUTE_N', '40': 'AMP_FAULT_N',
                 '30': '3V3_AMP', '31': '3V3_AMP', '14': '3V3_AMP', '28': 'DVDD_REG', '32': 'CP', '34': 'CN', '35': 'CPVSS',
                 '6': 'PVDD', '7': 'PVDD', '41': 'PVDD', '42': 'PVDD', '43': 'PVDD',
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    # control pins
    s.comp('R102', 'Device:R', '100k', (38.1, 106.68), nets={'1': '3V3_AMP', '2': 'AMP_FAULT_N'}, footprint=R0603,
           fields=F(spec='100 kOhm 1% 0603', note='SPK_FAULT pull-up (VOL spec uses 100 k)'))
    for i, (ref, net) in enumerate([('R103', 'AMP_GPIO0'), ('R104', 'AMP_GPIO1'), ('R105', 'AMP_GPIO2')]):
        s.comp(ref, 'Device:R', '100k', (55.88 + i * 12.7, 106.68), nets={'1': net, '2': 'GND'}, footprint=R0603,
               fields=F(spec='100 kOhm 1% 0603', note='unused GPIO held low'))
    tp(s, 'TP19', 'AMP_FAULT_N', 25.4, 106.68, 'FAULT')
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        'Overlay rpi-digiampplus: pcm5122@4c on i2c1, i2s_clk_producer, mute-gpios GPIO22 active high (driver sets 1 = unmute).',
        'Thermal pad: via array + paste windows 70-80 % of the pad area (SLAS988B 11.1.3.2) - footprint in block 2.',
        'No PVDD electrolytic at the amp (block 2, layout density): TI Table 22 says the 390 uF bulk "can be reduced or even removed";',
        '  C5 (120 uF on +20V) feeds PVDD through F5 (75 mOhm max, tau 9 us), plus 4 x 22 uF + 2 x 0.1 uF at the PVDD pins.']),
        25.4, 243.84)


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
